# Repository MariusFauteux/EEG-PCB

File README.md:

# EEG acquisition PCB

Portable eight-channel EEG recorder built around the TI ADS1299, for long-term comparison of PEDOT:PSS and Ag/AgCl electrodes. It records to microSD whilst streaming over BLE to a Mac.

**Status (2026-11-09):** Rev C12: datasheet review of the signal path and REF/BIAS electrode impedance test links (JP9, JP10) added to Step 14: VBUS overvoltage protection drawn, and the 110 × 85 mm four-layer board placed with stack-up, rules, keep-outs and planes. The board is not routed (Step 15). It passes KiCad DRC apart from the expected unrouted connections and a short list of individually accepted warnings, and it matches the schematic exactly. There is no firmware and no physical test. The board is not released for fabrication or for connection to a person.

## Where to start

| If you want to… | Read |
|---|---|
| Understand the design and why it is built this way | [docs/project.md](docs/project.md) |
| See every decision, its status and what would reopen it | [docs/decision_log.md](docs/decision_log.md) |
| Check the detailed calculations and sources for one subsystem | [docs/reviews/](docs/reviews/) |
| Open the schematic or board | [hardware/EEG_RevC.kicad_pro](hardware/EEG_RevC.kicad_pro) in KiCad 10 or later, the SVGs in [hardware/preview/](hardware/preview/), or the placement plots [hardware/checks/pcb_placement_top.pdf](hardware/checks/pcb_placement_top.pdf) and [pcb_inner_planes.pdf](hardware/checks/pcb_inner_planes.pdf) |
| See the parts list and cost | [hardware/bom.csv](hardware/bom.csv), [hardware/bom_cost.csv](hardware/bom_cost.csv) and [hardware/checks/bom_cost.md](hardware/checks/bom_cost.md) |
| See the latest check results | [hardware/checks/validation.md](hardware/checks/validation.md) and [hardware/checks/pcb_report.md](hardware/checks/pcb_report.md) |

## Folder layout

```
README.md                    status, map and open items (this file)
requirements.txt             Python packages for the build and checks
docs/
  project.md                 design guide for the current revision
  decision_log.md            current register, next actions, chronological entries
  recording_format_v1.md     microSD record format specification
  reviews/                   one review per design step (historical records)
hardware/
  EEG_RevC.kicad_pro/.sch    KiCad project; all *.kicad_sch files are generated
  EEG_RevC.kicad_pcb/.kicad_dru  placed board and custom design rules (generated by scripts/pcb_place.py)
  EEG.kicad_sym, sym-lib-table   project symbol library (generated)
  EEG.pretty, fp-lib-table   project footprint library (generated from manufacturer drawings)
  bom.csv                    bill of materials with manufacturer, MPN and description (generated)
  bom_cost.csv               costed BOM for 5 prototype boards (generated)
  controller_pinmap.csv      NINA-B306 pin allocation (generated)
  rebuild.sh                 regenerate everything and run all checks
  scripts/                   schematic generator, part selection, footprint generator, sheet layout and grouping, netlist validation, footprint audit, corner review, BOM cost, input and reference, backfeed, BIAS loop, timing, power and OVP analysis, board placement and DRC summary
  baseline/                  inputs the generator imports, and earlier netlists it compares against
  checks/                    generated: netlist, ERC report, validation report, footprint audit, corner review, BOM cost, analysis output, DRC report, placement report and plots
  preview/                   generated: SVG render of every sheet
host/
  record_format.py           host-side reference codec and recovery scanner for the record format
  test_record_format.py      codec tests
  event_timing.py            EVENT schema validation, session clock fit, event-to-sample mapping
  test_event_timing.py       event timing tests
```

The schematic sheets are generated by `hardware/scripts/build.py`. Edits made by hand in the KiCad editor are overwritten on the next rebuild, so a schematic change belongs in the scripts. A final layout pass (`hardware/scripts/layout.py`) arranges every sheet into dashed frames, one per functional block, each with a title and a short purpose note, and points labels away from the parts. The groups and notes are defined in `hardware/scripts/layout_groups.py`; a new part must be added to a group there or the build fails.

## Rebuilding and checking

One-time setup from this folder:

```bash
python3 -m venv .venv && .venv/bin/pip install -r requirements.txt
```

Then regenerate the schematic, export the netlist, run ERC, render the previews, generate and check the board, and run every check:

```bash
hardware/rebuild.sh
```

The script finds `kicad-cli` on the PATH or in `/Applications/KiCad`; set `KICAD_CLI` to override. The board script needs KiCad's own Python with the `pcbnew` module; set `KICAD_PY` if it is not in the macOS application bundle. A full rebuild takes about four minutes, mostly the board DRC with its creepage check. The footprint audit uses the KiCad 10 stock footprint library (set `KICAD10_FOOTPRINT_DIR` if it is elsewhere). The current result is:

- 486 netlist assertions passing and zero ERC errors;
- the footprint audit passing for all 377 on-board parts;
- 17 of 17 OVP rules and 27 of 27 corner-review rules passing;
- all input, backfeed and power-analysis rules passing;
- 33 of 33 placement rules passing;
- board DRC with no errors, 0 schematic-parity differences, 499 unrouted connections and 30 accepted warnings;
- passing host tests. ERC reports no warnings once KiCad has a global footprint-library table. On a fresh KiCad installation without one, expect a few hundred "the current configuration does not include the footprint library …" warnings; KiCad offers to create the table on first launch of the GUI, and the warnings do not indicate a circuit fault.

## Design history

| Step | Revision | What changed | Review |
|---|---|---|---|
| 1–2 | Rev A, Rev B | Input network, ADS1299 core, battery regulators and supervision | [revB_engineering_review.md](docs/reviews/revB_engineering_review.md) |
| 1–3 (Rev C) | Architecture | Operating modes, NINA-B306 selection, USB-C charging architecture | [revC_architecture_steps1-3.md](docs/reviews/revC_architecture_steps1-3.md) |
| 4 | C1 | LT3045 analogue rail, TPS389001 supervisors, hardware reset gating | [step4_power_review.md](docs/reviews/step4_power_review.md) |
| 5 | C2 | Controller, SWD, USB-C data and CC detection, digital rail | [step5_controller_usb_review.md](docs/reviews/step5_controller_usb_review.md) |
| 6 | C3 | microSD, shutdown behaviour, recording format | [step6_storage_shutdown_review.md](docs/reviews/step6_storage_shutdown_review.md) |
| 7 | C4 | Electrode input protection and filtering | [step7_input_protection_review.md](docs/reviews/step7_input_protection_review.md) |
| 8 | C5 | BIAS loop compensation and output clamp | [step8_bias_review.md](docs/reviews/step8_bias_review.md) |
| 9 | C6 | External 2.048 MHz ADC clock, isolated trigger, photodiode front end, timestamp scheme | [step9_event_timing_review.md](docs/reviews/step9_event_timing_review.md) |
| 10 | C7 | Analogue rail 5.088 V (45.9 mV release margin), restart latch, Schmitt-input reset logic, power capacitor selection | [step10_power_review.md](docs/reviews/step10_power_review.md) |
| 11 | C8 | BQ25798 charger and power path, hardware input ceiling < 500 mA, ship FET soft-off and POWER button, pack connector with NTC, SYS hold-up | [step11_charger_review.md](docs/reviews/step11_charger_review.md) |
| 12 | C9 | OPA376 buffer for the shared REF electrode (coupling −37.3 dB → below −150 dB modelled; SRB1 rejected), self-biased clamp holding +5VA ≤ 1.3 V when off (was up to 6.9 V at 100 V between electrodes) | [step12_reference_backfeed_review.md](docs/reviews/step12_reference_backfeed_review.md) |
| 13 | C10 | Exact MPN for all 360 fitted parts (€188 per board in parts at 5 boards), five project footprints from manufacturer drawings and an automated pin-to-pad audit, shell pads fixed on USB-C and microSD, E96 values for RSET and two supervisor dividers, electrode harness connector J500, whole-netlist corner review | [step13_bom_footprint_review.md](docs/reviews/step13_bom_footprint_review.md) |
| 14 | C11 | VBUS overvoltage switch TPD1S514-1 (trips 5.90–5.99 V in 100 ns, 30 V rated) with a 5.0 V LDO for the module VBUS pad. Board 110 × 85 mm one-sided on the JLC04161H-3313 stack-up, JLCPCB rules and netclasses, antenna and 8 mm trigger keep-outs, planes. All 375 parts placed by a generated script; DRC clean apart from unrouted nets | [step14_ovp_placement_review.md](docs/reviews/step14_ovp_placement_review.md) |
| 14a | C12 | Pin-by-pin datasheet review of the ADS1299, OPA376 and TPD2E2U06 (all pass; LT3045 still unread). JP9 and JP10 let the REF and BIAS electrodes be measured by the ADS1299 lead-off sources through CH8−/CH7− | [revC12_datasheet_impedance_review.md](docs/reviews/revC12_datasheet_impedance_review.md) |
| 15 | (next) | Routing: freeze placement, 90 Ω USB pair, plane vias, converter loops, assembly outputs | |

The reviews are kept as written at each step. They refer to file names used at the time (for example `build_step7.py`, `EEG_RevC_Step7.kicad_sch` and the per-step zip packages). Those names now correspond to `build.py`, `EEG_RevC.kicad_sch` and this folder.

## Open items and release gates

Nothing below has been closed by measurement. The Rev B review findings R01–R12 remain formally open; most are now addressed in the schematic but await physical evidence.

| # | Item | Notes |
|---:|---|---|
| 1 | BIAS loop bench validation | Step 8 compensation is model-based (≥ 47° modelled margin); measure step response, mains rejection and saturation recovery with an electrode simulator. RB1/RB2 and the electrode resistors are ERJ-PB6B thick film (150 V element voltage, Step 13); ESD and surge capability still to be tested |
| 2 | Power and supervision bench validation | Step 10 closed the Step 4 review by calculation: confirm VOUT over temperature, supervisor thresholds, pack-disconnect sequence and the restart latch under battery rebound; DC-bias curves read in Step 13 (C203 + C204 26 µF worst case); capacitance over temperature still to measure |
| 3 | Charger and pack qualification | Step 11 drew the BQ25798 path; pack (2S, protected, 10k 103AT NTC) not chosen; VQFN-HR footprint drawn from TI's land pattern (Step 13, check 1:1 before release); check ship-mode leakage and charging thermals on the bench |
| 4 | Event timing bench validation | Step 9 is datasheet-based: calibrate ADC group delay (assumed 1.5 samples) and input latencies by loopback; confirm the proposed timing targets T1–T3; J600/J601 connectors chosen provisionally (Step 13); trigger isolation adequacy for participant use not assessed |
| 5 | Shared-REF channel coupling | Step 12 buffered REF (D46): modelled coupling below −150 dB. Measure crosstalk, buffer noise and REF lead-off behaviour with an electrode emulator |
| 6 | Powered-off backfeed | Step 12 clamp Q201 (D47): AVDD ≤ 1.3 V modelled up to 100 V between electrodes. Inject in ship mode and with the rail disabled; YJC footprint drawn (Step 13); re-read the LT3045 reverse-current data |
| 7 | Mechanical service interlock | Prevent USB insertion with the electrode harness attached; not designed |
| 8 | BOM and footprints | Closed at design level (Step 13, extended in Step 14): 393 references, 368 fitted with exact MPNs, 0 without footprint; 6 project footprints. Still needed: 1:1 or part comparison of the project footprints (including the 0.4 mm WCSP of U323), estimated heights, and the 4 % of the cost not yet confirmed; C324's MPN is on backorder at DigiKey (in-stock KEMET alternative named in the Step 14 review) |
| 9 | microSD shell pads in KiCad 10 | Closed (Step 13): symbol pin renamed `SH`; the same fault on the USB-C connector was found and fixed |
| 10 | Firmware | No MCU acquisition, BLE or SD firmware; host codec only. Firmware must set BIASREF_INT = 1 when enabling the BIAS amplifier (Step 8) and implement the TIMER3/GPIOTE/PPI capture scheme and EVENT records (Step 9). Restart needs a fresh RUN_REQUEST rising edge, and the last 5 samples before a supervisor stop are invalid (Step 10). Charger: raise IINDPM only after reading the TUSB320 advertisement, set charge and JEITA limits, handle the watchdog, enter ship mode for soft-off (Step 11). Fit JP 2–3 for referential channels with SRB1/SRB2 off, detect REF lead-off from all referential channels drifting together, and wait 1 s after an analogue stop before re-arming (Step 12). Impedance: AC lead-off at 7.8 or 31.2 Hz with 6 or 24 nA, excited channel removed from BIAS_SENS, series resistance subtracted (Rev C12). Run the power I²C bus at 100 kHz unless the layout keeps it below ≈ 70 pF (Step 13) |
| 11 | Routing, prototype and qualification | Board placed (Step 14); routing next (Step 15) under the rules in the Step 14 review, section 8. Then noise, leakage, ESD, endurance, power-loss and safety testing |
| 12 | VBUS overvoltage | Closed at design level (Step 14, D57): TPD1S514-1 limits USB_5V to 6.15 V worst case. Still needed: bench overvoltage and hot-plug test; WCSP assembly check; firmware keeps EN_OTG = 0 |
| 13 | Board area and pack position | Closed (Step 14, D56): 110 × 85 mm, one-sided, courtyards 51 %; pack beside the board on J401. Enclosure still to design |

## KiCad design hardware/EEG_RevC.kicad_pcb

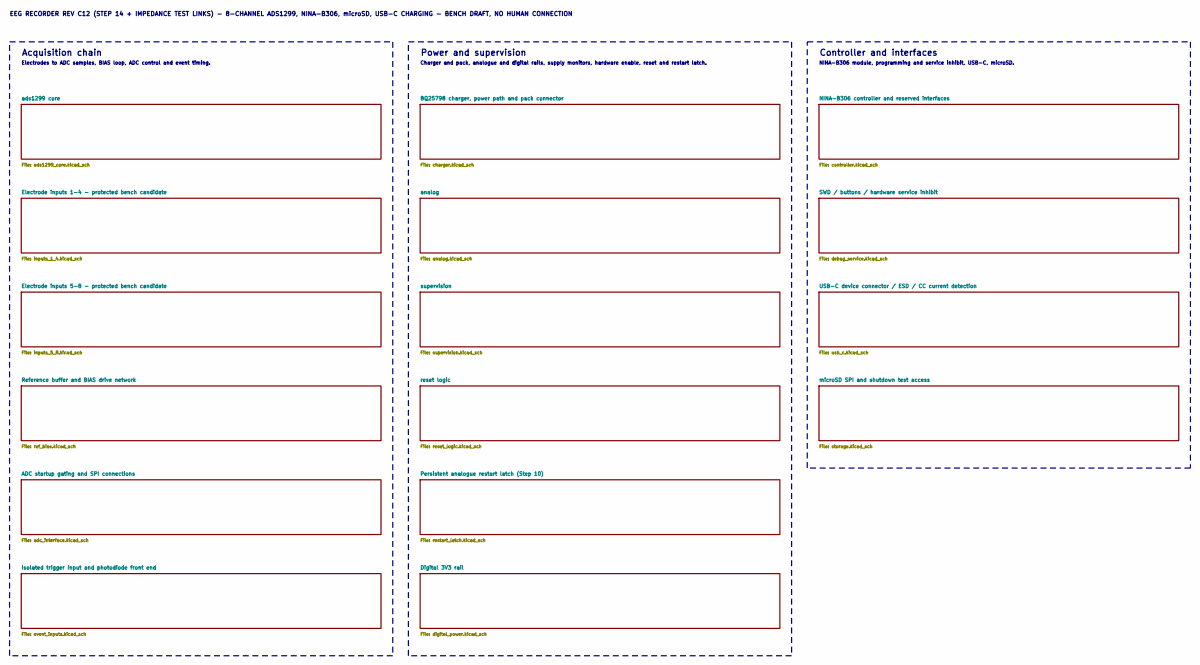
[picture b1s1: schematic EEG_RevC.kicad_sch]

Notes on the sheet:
Acquisition chain
Electrodes to ADC samples, BIAS loop, ADC control and event timing.
Power and supervision
Charger and pack, analogue and digital rails, supply monitors, hardware enable, reset and restart latch.
Controller and interfaces
NINA-B306 module, programming and service inhibit, USB-C, microSD.
EEG RECORDER REV C12 (STEP 14 + IMPEDANCE TEST LINKS) - 8-CHANNEL ADS1299, NINA-B306, microSD, USB-C CHARGING - BENCH DRAFT, NO HUMAN CONNECTION

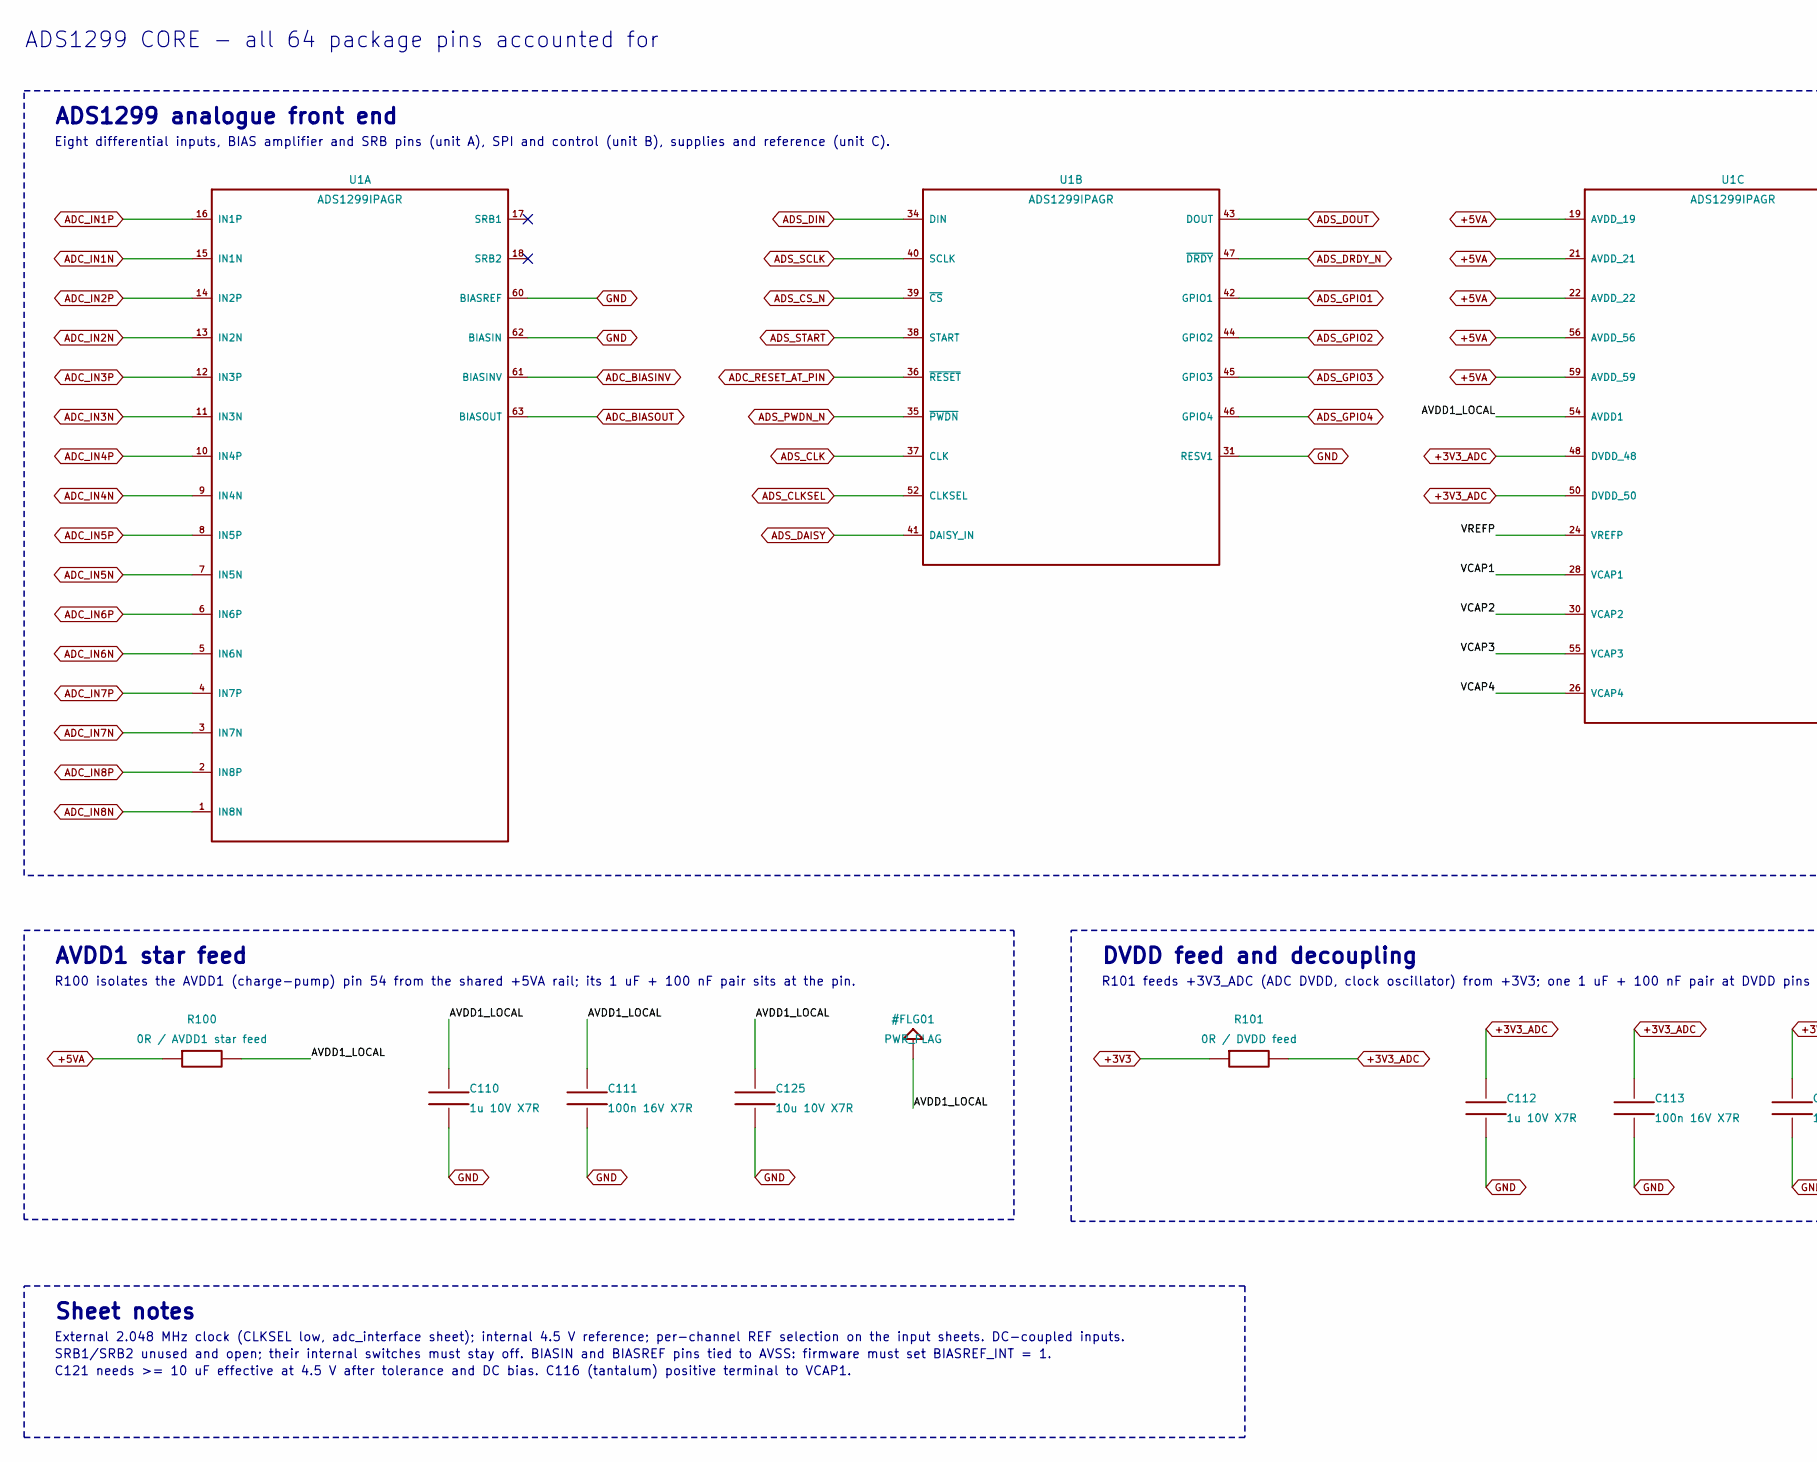
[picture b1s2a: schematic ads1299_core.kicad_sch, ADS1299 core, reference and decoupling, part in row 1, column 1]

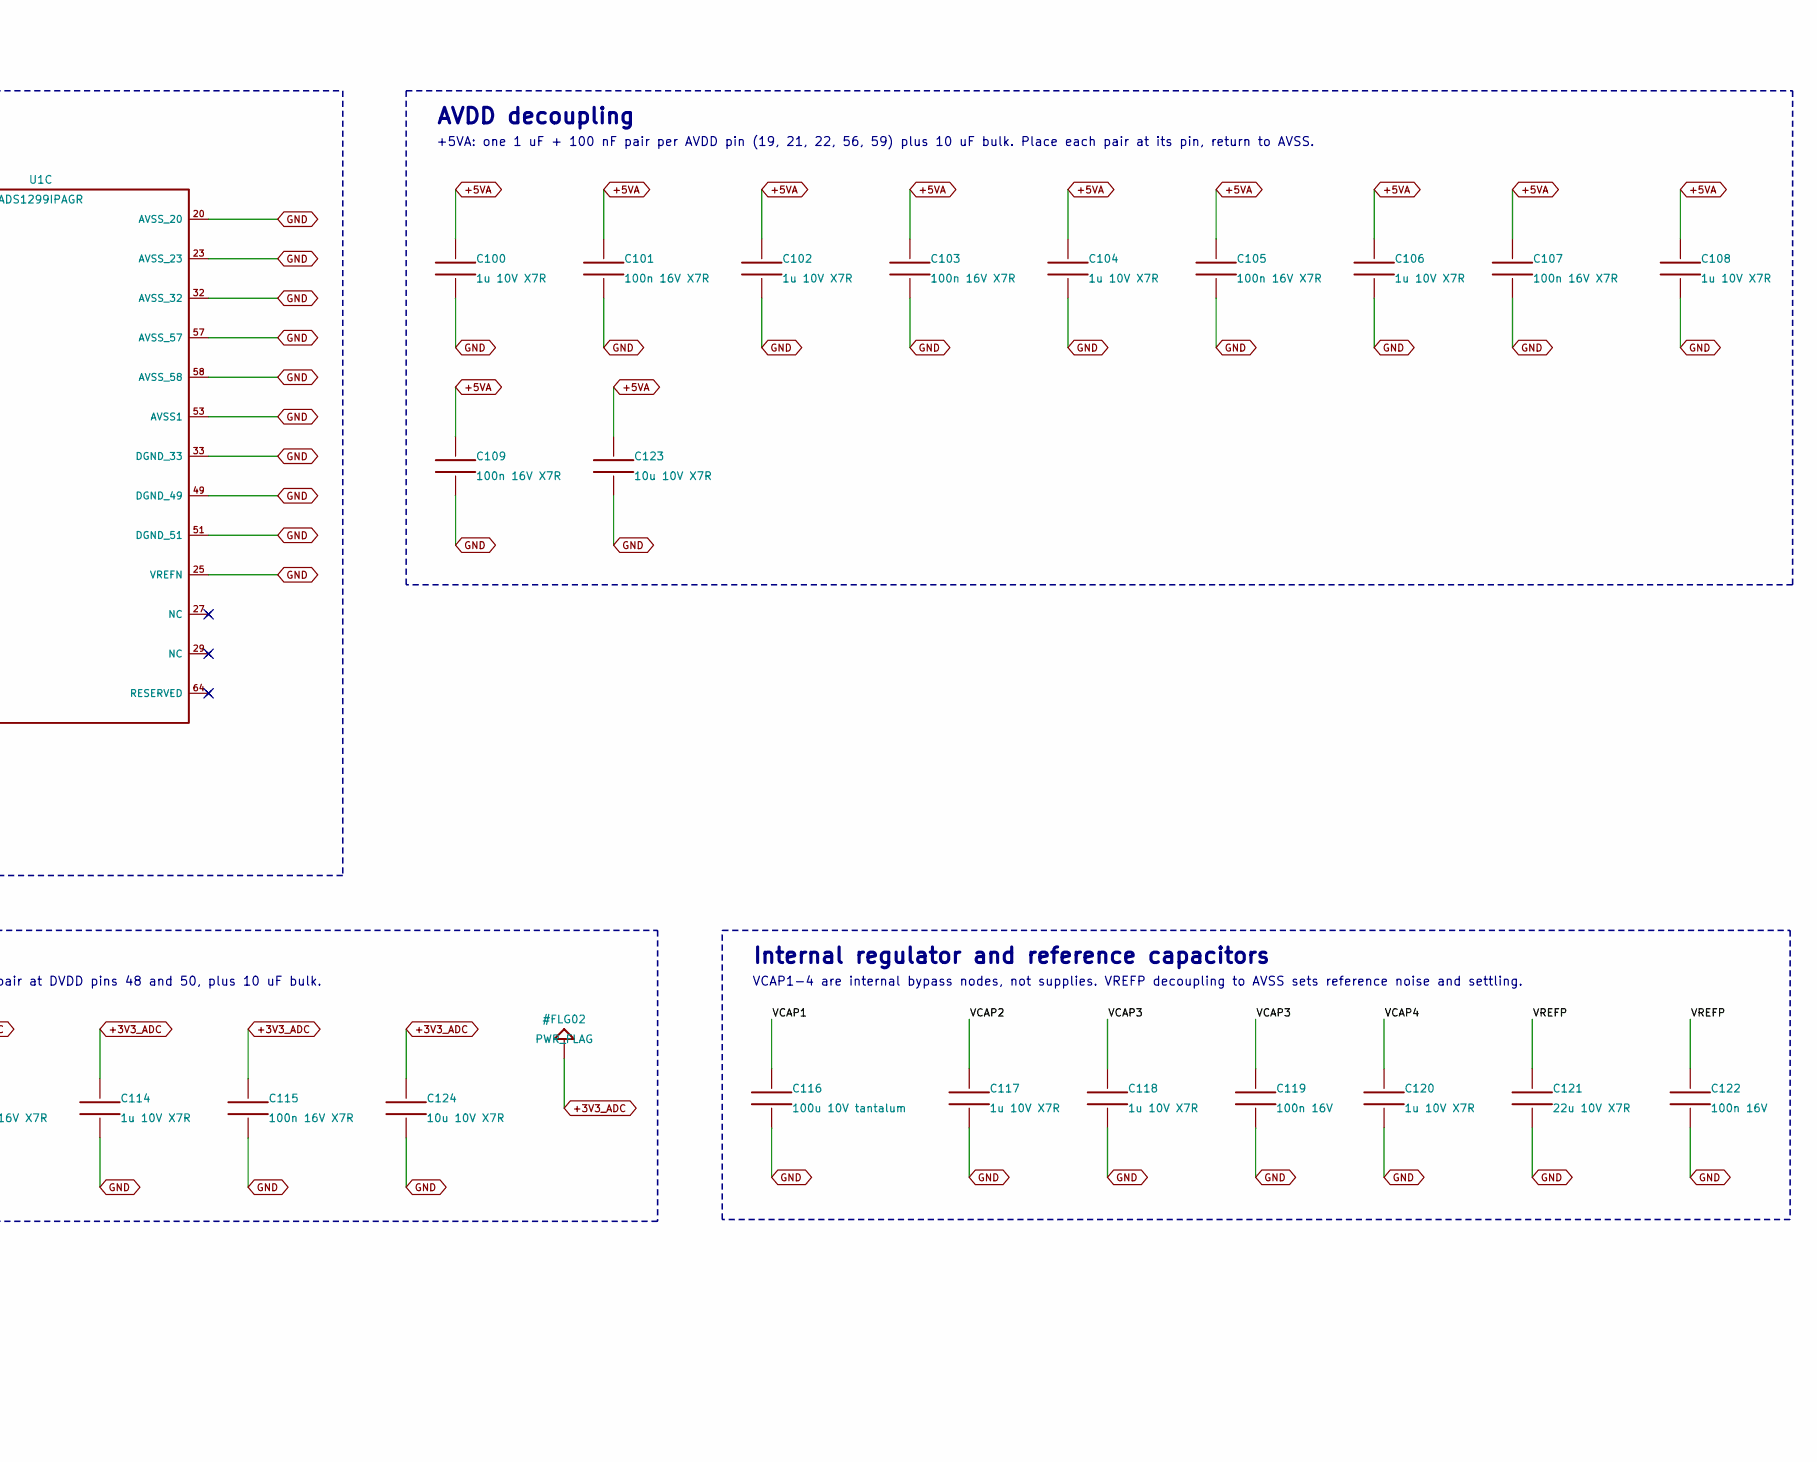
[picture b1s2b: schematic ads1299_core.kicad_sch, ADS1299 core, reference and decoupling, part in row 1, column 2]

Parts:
C100, C102, C104, C106, C108, C110, C112, C114, C117, C118, C120: 1u 10V X7R; C_0805_2012Metric; MPN GCM21BR71E105KA56L
C101, C103, C105, C107, C109, C111, C113, C115: 100n 16V X7R; C_0603_1608Metric; MPN GCM188R71H104KA57D
C116: 100u 10V tantalum; CP_EIA-7343-31_Kemet-D; MPN T491D107K010AT
C119, C122: 100n 16V; C_0603_1608Metric; MPN GCM188R71H104KA57D
C121: 22u 10V X7R; C_1210_3225Metric; MPN GRM32ER71E226KE15L
C123, C124, C125: 10u 10V X7R; C_1206_3216Metric; MPN GRM31CR71E106KA12L
R100: 0R / AVDD1 star feed; R_0603_1608Metric; MPN ERJ-3GEY0R00V
R101: 0R / DVDD feed; R_0603_1608Metric; MPN ERJ-3GEY0R00V
U1: ADS1299IPAGR; TQFP-64_10x10mm_P0.5mm; MPN ADS1299IPAGR

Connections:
+3V3: R101.1; also elsewhere on the board
+3V3_ADC: C112.1, C113.1, C114.1, C115.1, C124.1, R101.2, U1.48 (DVDD_48), U1.50 (DVDD_50); also elsewhere on the board
+5VA: C100.1, C101.1, C102.1, C103.1, C104.1, C105.1, C106.1, C107.1, C108.1, C109.1, C123.1, R100.1, U1.19 (AVDD_19), U1.21 (AVDD_21), U1.22 (AVDD_22), U1.56 (AVDD_56), U1.59 (AVDD_59); also elsewhere on the board
/ads1299 core/AVDD1_LOCAL: C110.1, C111.1, C125.1, R100.2, U1.54 (AVDD1)
/ads1299 core/VCAP1: C116.1, U1.28 (VCAP1)
/ads1299 core/VCAP2: C117.1, U1.30 (VCAP2)
/ads1299 core/VCAP3: C118.1, C119.1, U1.55 (VCAP3)
/ads1299 core/VCAP4: C120.1, U1.26 (VCAP4)
/ads1299 core/VREFP: C121.1, C122.1, U1.24 (VREFP)
ADC_BIASINV: U1.61 (BIASINV); also elsewhere on the board
ADC_BIASOUT: U1.63 (BIASOUT); also elsewhere on the board
ADC_IN1N: U1.15 (IN1N); also elsewhere on the board
ADC_IN1P: U1.16 (IN1P); also elsewhere on the board
ADC_IN2N: U1.13 (IN2N); also elsewhere on the board
ADC_IN2P: U1.14 (IN2P); also elsewhere on the board
ADC_IN3N: U1.11 (IN3N); also elsewhere on the board
ADC_IN3P: U1.12 (IN3P); also elsewhere on the board
ADC_IN4N: U1.9 (IN4N); also elsewhere on the board
ADC_IN4P: U1.10 (IN4P); also elsewhere on the board
ADC_IN5N: U1.7 (IN5N); also elsewhere on the board
ADC_IN5P: U1.8 (IN5P); also elsewhere on the board
ADC_IN6N: U1.5 (IN6N); also elsewhere on the board
ADC_IN6P: U1.6 (IN6P); also elsewhere on the board
ADC_IN7N: U1.3 (IN7N); also elsewhere on the board
ADC_IN7P: U1.4 (IN7P); also elsewhere on the board
ADC_IN8N: U1.1 (IN8N); also elsewhere on the board
ADC_IN8P: U1.2 (IN8P); also elsewhere on the board
ADC_RESET_AT_PIN: U1.36 (~RESET); also elsewhere on the board
ADS_CLK: U1.37 (CLK); also elsewhere on the board
ADS_CLKSEL: U1.52 (CLKSEL); also elsewhere on the board
ADS_CS_N: U1.39 (~CS); also elsewhere on the board
ADS_DAISY: U1.41 (DAISY_IN); also elsewhere on the board
ADS_DIN: U1.34 (DIN); also elsewhere on the board
ADS_DOUT: U1.43 (DOUT); also elsewhere on the board
ADS_DRDY_N: U1.47 (~DRDY); also elsewhere on the board
ADS_GPIO1: U1.42 (GPIO1); also elsewhere on the board
ADS_GPIO2: U1.44 (GPIO2); also elsewhere on the board
ADS_GPIO3: U1.45 (GPIO3); also elsewhere on the board
ADS_GPIO4: U1.46 (GPIO4); also elsewhere on the board
ADS_PWDN_N: U1.35 (~PWDN); also elsewhere on the board
ADS_SCLK: U1.40 (SCLK); also elsewhere on the board
ADS_START: U1.38 (START); also elsewhere on the board
GND: C100.2, C101.2, C102.2, C103.2, C104.2, C105.2, C106.2, C107.2, C108.2, C109.2, C110.2, C111.2, C112.2, C113.2, C114.2, C115.2, C116.2, C117.2, C118.2, C119.2, C120.2, C121.2, C122.2, C123.2, C124.2, C125.2, U1.20 (AVSS_20), U1.23 (AVSS_23), U1.25 (VREFN), U1.31 (RESV1), U1.32 (AVSS_32), U1.33 (DGND_33), U1.49 (DGND_49), U1.51 (DGND_51), U1.53 (AVSS1), U1.57 (AVSS_57), U1.58 (AVSS_58), U1.60 (BIASREF), U1.62 (BIASIN); also elsewhere on the board

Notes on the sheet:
ADS1299 CORE - all 64 package pins accounted for
ADS1299 analogue front end
Eight differential inputs, BIAS amplifier and SRB pins (unit A), SPI and control (unit B), supplies and reference (unit C).
AVDD decoupling
+5VA: one 1 uF + 100 nF pair per AVDD pin (19, 21, 22, 56, 59) plus 10 uF bulk. Place each pair at its pin, return to AVSS.
AVDD1 star feed
R100 isolates the AVDD1 (charge-pump) pin 54 from the shared +5VA rail; its 1 uF + 100 nF pair sits at the pin.
DVDD feed and decoupling
R101 feeds +3V3_ADC (ADC DVDD, clock oscillator) from +3V3; one 1 uF + 100 nF pair at DVDD pins 48 and 50, plus 10 uF bulk.
Internal regulator and reference capacitors
VCAP1-4 are internal bypass nodes, not supplies. VREFP decoupling to AVSS sets reference noise and settling.
Sheet notes
External 2.048 MHz clock (CLKSEL low, adc_interface sheet); internal 4.5 V reference; per-channel REF selection on the input sheets. DC-coupled inputs.
SRB1/SRB2 unused and open; their internal switches must stay off. BIASIN and BIASREF pins tied to AVSS: firmware must set BIASREF_INT = 1.
C121 needs >= 10 uF effective at 4.5 V after tolerance and DC bias. C116 (tantalum) positive terminal to VCAP1.

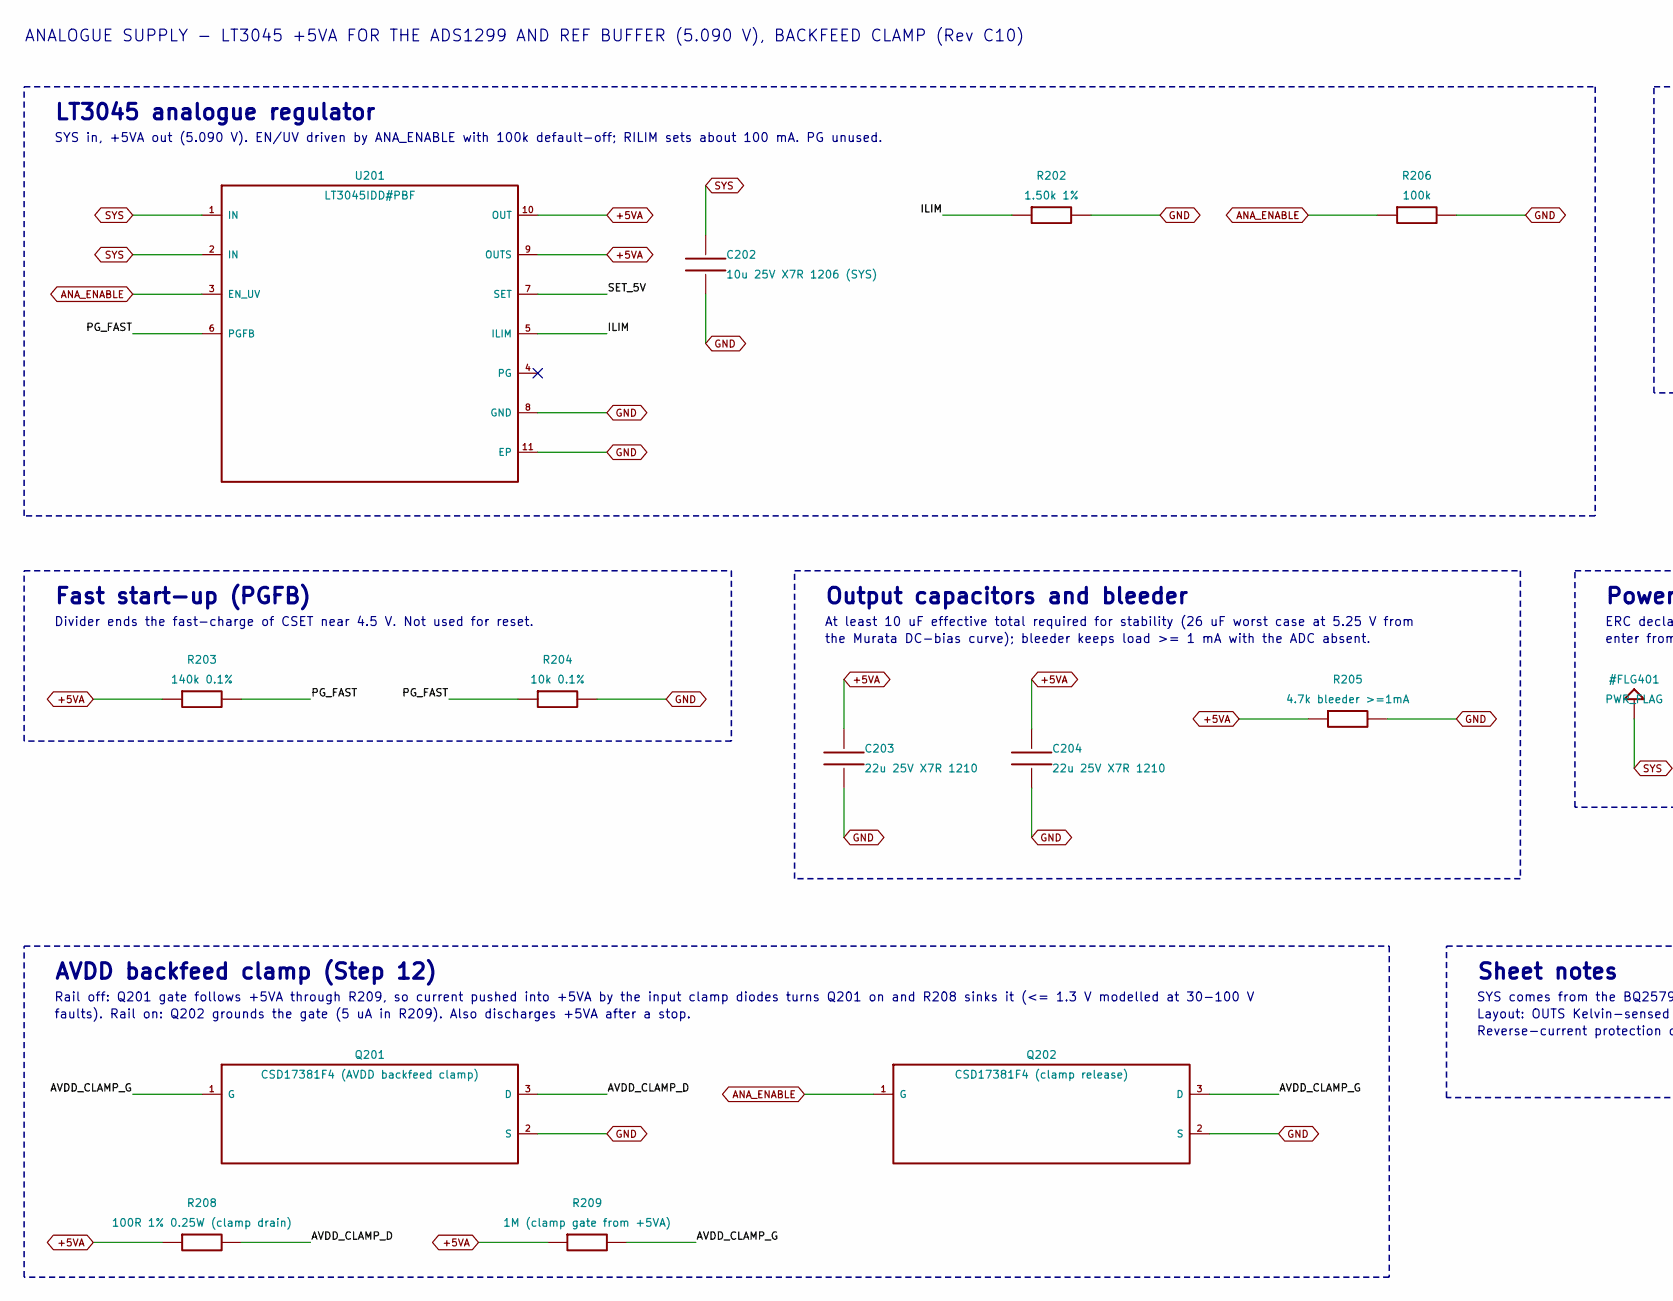
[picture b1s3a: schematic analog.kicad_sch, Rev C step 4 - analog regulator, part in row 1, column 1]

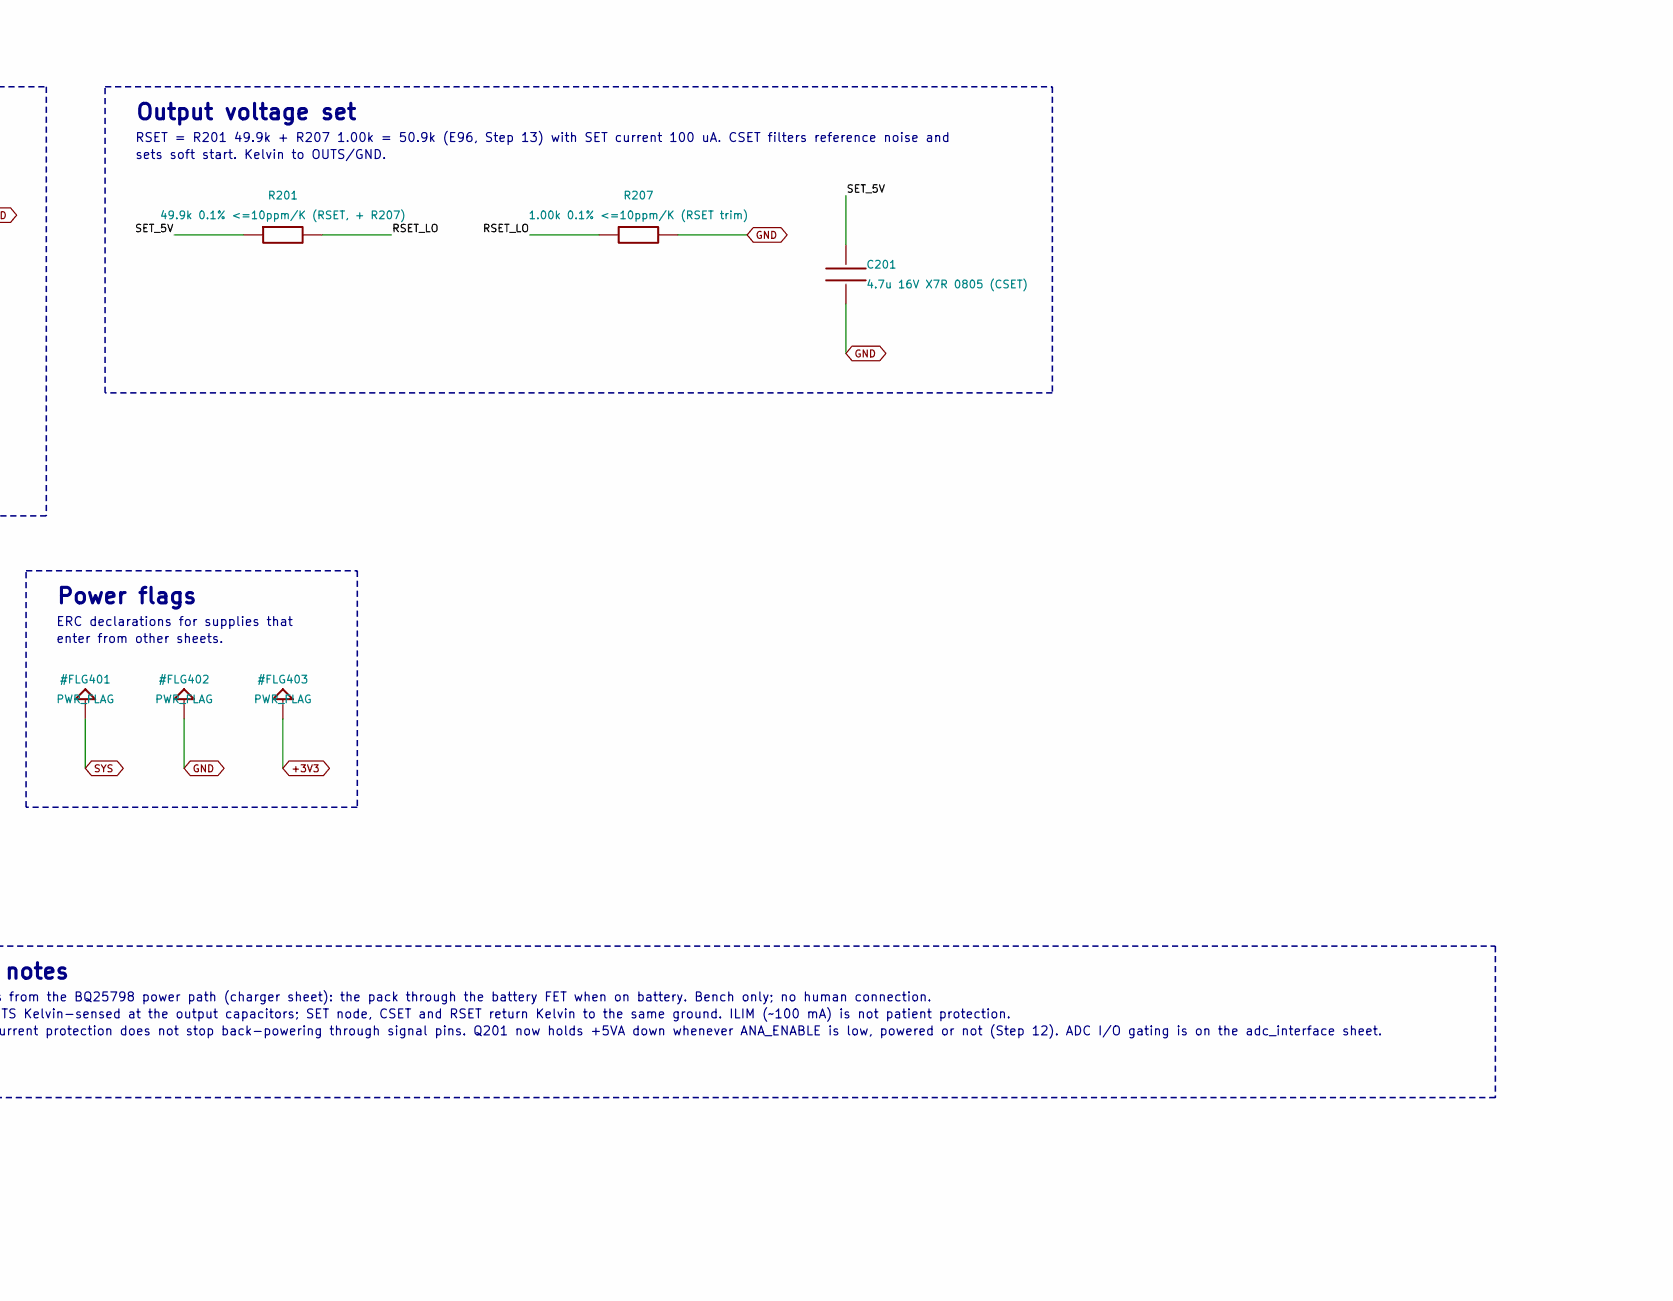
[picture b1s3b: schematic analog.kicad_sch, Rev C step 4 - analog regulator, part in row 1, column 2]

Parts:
C201: 4.7u 16V X7R 0805 (CSET); C_0805_2012Metric; MPN GRM21BR71C475KE51L
C202: 10u 25V X7R 1206 (SYS); C_1206_3216Metric; MPN GRM31CR71E106KA12L
C203, C204: 22u 25V X7R 1210; C_1210_3225Metric; MPN GRM32ER71E226KE15L
Q201: CSD17381F4 (AVDD backfeed clamp); Texas_YJC0003A_FemtoFET-3_1.0x0.6mm; MPN CSD17381F4
Q202: CSD17381F4 (clamp release); Texas_YJC0003A_FemtoFET-3_1.0x0.6mm; MPN CSD17381F4
R201: 49.9k 0.1% <=10ppm/K (RSET, + R207); R_0603_1608Metric; MPN ERA-3ARB4992V
R202: 1.50k 1%; R_0603_1608Metric; MPN ERJ-3EKF1501V
R203: 140k 0.1%; R_0603_1608Metric; MPN ERA-3AEB1403V
R204: 10k 0.1%; R_0603_1608Metric; MPN ERA-3ARB103V
R205: 4.7k bleeder >=1mA; R_0603_1608Metric; MPN ERJ-3EKF4701V
R206: 100k; R_0603_1608Metric; MPN ERJ-3EKF1003V
R207: 1.00k 0.1% <=10ppm/K (RSET trim); R_0603_1608Metric; MPN ERA-3ARB102V
R208: 100R 1% 0.25W (clamp drain); R_1206_3216Metric; MPN ERJ-8ENF1000V
R209: 1M (clamp gate from +5VA); R_0603_1608Metric; MPN ERJ-3EKF1004V
U201: LT3045IDD#PBF; DFN-10-1EP_3x3mm_P0.5mm_EP1.65x2.38mm; MPN LT3045IDD#PBF

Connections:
+5VA: C203.1, C204.1, R203.1, R205.1, R208.1, R209.1, U201.9 (OUTS), U201.10 (OUT); also elsewhere on the board
/analog/AVDD_CLAMP_D: Q201.3 (D), R208.2
/analog/AVDD_CLAMP_G: Q201.1 (G), Q202.3 (D), R209.2
/analog/ILIM: R202.1, U201.5 (ILIM)
/analog/PG_FAST: R203.2, R204.1, U201.6 (PGFB)
/analog/RSET_LO: R201.2, R207.1
/analog/SET_5V: C201.1, R201.1, U201.7 (SET)
ANA_ENABLE: Q202.1 (G), R206.1, U201.3 (EN_UV); also elsewhere on the board
GND: C201.2, C202.2, C203.2, C204.2, Q201.2 (S), Q202.2 (S), R202.2, R204.2, R205.2, R206.2, R207.2, U201.8 (GND), U201.11 (EP); also elsewhere on the board
SYS: C202.1, U201.1 (IN), U201.2 (IN); also elsewhere on the board

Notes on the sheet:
ANALOGUE SUPPLY - LT3045 +5VA FOR THE ADS1299 AND REF BUFFER (5.090 V), BACKFEED CLAMP (Rev C10)
LT3045 analogue regulator
SYS in, +5VA out (5.090 V). EN/UV driven by ANA_ENABLE with 100k default-off; RILIM sets about 100 mA. PG unused.
Output voltage set
RSET = R201 49.9k + R207 1.00k = 50.9k (E96, Step 13) with SET current 100 uA. CSET filters reference noise and
sets soft start. Kelvin to OUTS/GND.
Fast start-up (PGFB)
Divider ends the fast-charge of CSET near 4.5 V. Not used for reset.
Output capacitors and bleeder
At least 10 uF effective total required for stability (26 uF worst case at 5.25 V from
the Murata DC-bias curve); bleeder keeps load >= 1 mA with the ADC absent.
Power flags
ERC declarations for supplies that
enter from other sheets.
AVDD backfeed clamp (Step 12)
Rail off: Q201 gate follows +5VA through R209, so current pushed into +5VA by the input clamp diodes turns Q201 on and R208 sinks it (<= 1.3 V modelled at 30-100 V
faults). Rail on: Q202 grounds the gate (5 uA in R209). Also discharges +5VA after a stop.
Sheet notes
SYS comes from the BQ25798 power path (charger sheet): the pack through the battery FET when on battery. Bench only; no human connection.
Layout: OUTS Kelvin-sensed at the output capacitors; SET node, CSET and RSET return Kelvin to the same ground. ILIM (~100 mA) is not patient protection.
Reverse-current protection does not stop back-powering through signal pins. Q201 now holds +5VA down whenever ANA_ENABLE is low, powered or not (Step 12). ADC I/O gating is on the adc_interface sheet.
